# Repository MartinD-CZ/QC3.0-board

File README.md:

# QC3.0 board
*see the article [here](http://embedblog.eu/?p=504). Also available on [Tindie](https://www.tindie.com/products/martind/quick-charge-qc-30-buck-converter-board/).*

Board with a switching buck converter and a QC 3.0 class-A chip (it also supports FastCharge, DCP, and others).

## Features:
* HiSilicon Fast Charging Protocol (FCP), ie Huawei phones (tested)
* Qualcomm Quick Charge 2.0/3.0 Class A: up to 12 V Output Voltage (tested)
* USB DCP (shorting D+ Line to D-) per USB Battery Charging Specification, Revision 1.2 (tested)
* USB DCP (applying 2.7V on D+ Line and 2.7V on D- Line), ie Apple 12 W
* USB DCP (applying 1.2V on D+ and D- Lines)
* Chinese Telecommunication Industrial Standard YD/T 1591-2009 (whatever that is, I have not tested that)

## Specs:
* input voltage: 6 - 15 V, recommended 12 - 15 V
* input current: max 2 A
* output current: max 2 A
* efficiency (Vin = 12 V, Vout = 5 V, Iout = 1 A): 95 %
* efficiency (Vin = 12 V, Vout = 5 V, Iout = 2 A): 92 %
* quiescent current (no load connected, Vin = 12 V): 800 µA

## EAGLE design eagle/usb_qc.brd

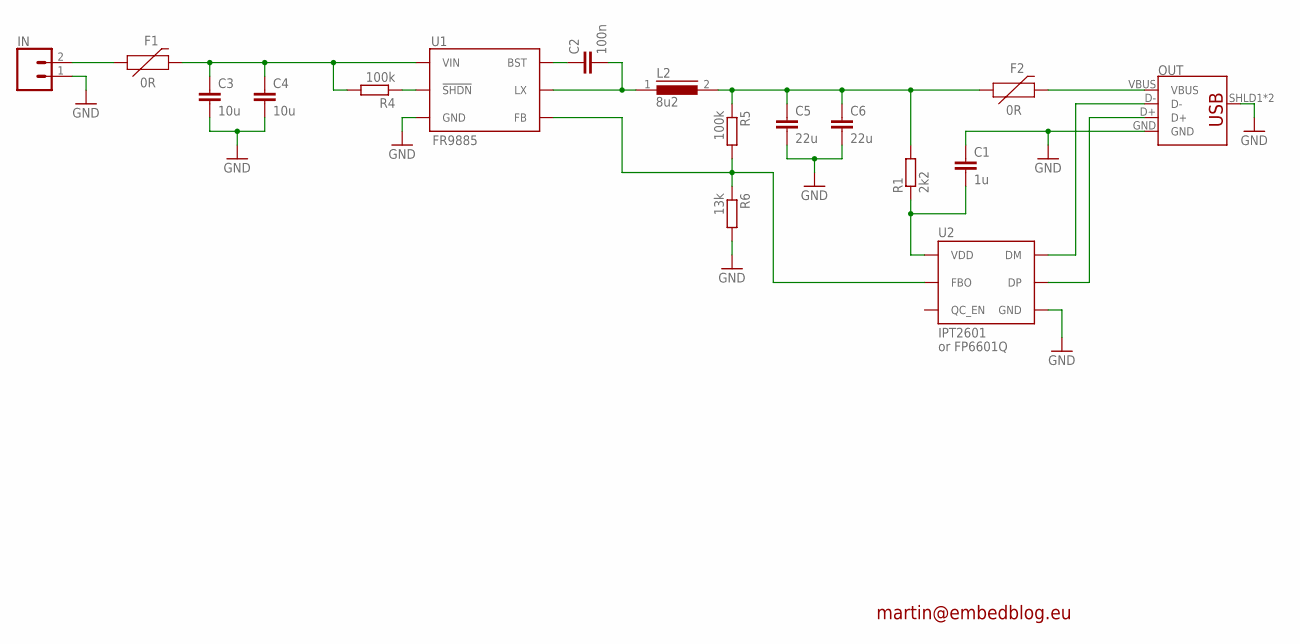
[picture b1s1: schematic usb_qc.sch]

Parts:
C1: 1u; C1206
C2: 100n; C1206
C3, C4: 10u; C1206
C5, C6: 22u; C1206
F1, F2: 0R; 1206
IN: 5MM_SCREWTERMINAL_LARGE; SCREWTERMINAL-5MM-2
L2: 8u2; DR73
OUT: USB_A_REVERSED; USB-A-S-SILK-FEMALE
R1: 2k2; R1206
R4, R5: 100k; R1206
R6: 13k; R1206
U1: FR9885; SOT23-6
U2: IPT2601; SOT23-6

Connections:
FB: R5.2, R6.1, U1.3 (FB), U2.3 (FBO)
GND: C1.1, C3.2, C4.2, C5.2, C6.2, IN.1, OUT.GND, OUT.SHLD1 (SHIELD), OUT.SHLD2 (SHIELD), R6.2, U1.2 (GND), U2.2 (GND)
LX: C2.2, L2.1, U1.6 (LX)
unnamed: OUT.D-, U2.6 (DM)
unnamed: OUT.D+, U2.1 (DP)
unnamed: F1.1, IN.2
unnamed: C3.1, C4.1, F1.2, R4.2, U1.5 (VIN)
unnamed: R4.1, U1.4 (!SHDN)
unnamed: C5.1, C6.1, F2.1, L2.2, R1.2, R5.1
unnamed: C1.2, R1.1, U2.5 (VDD)
unnamed: C2.1, U1.1 (BST)
VBUS: F2.2, OUT.VBUS

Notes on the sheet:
or FP6601Q
martin@embedblog.eu

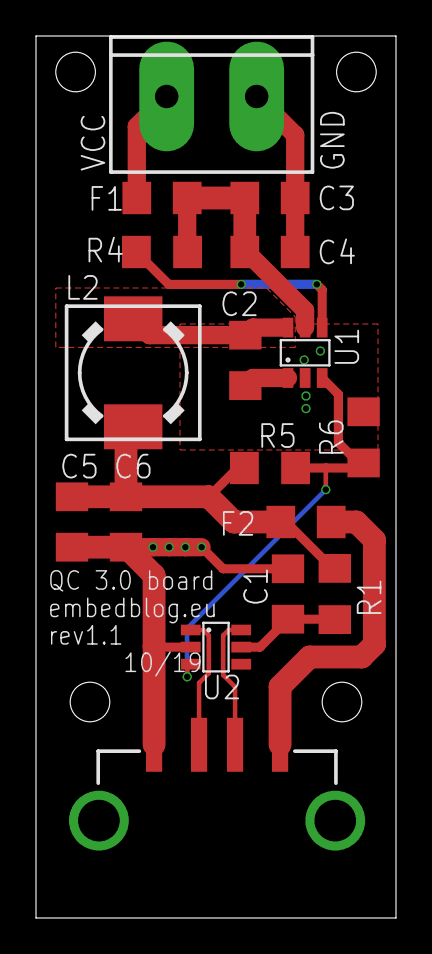
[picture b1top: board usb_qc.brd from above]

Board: 2 copper layers, 20.0 x 49.0 mm, 17 parts (0 on the bottom side), 12 nets.

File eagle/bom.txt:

Part Value                   Device                  Package             Description                                             
C1   1u                      C-EUC1206               C1206               CAPACITOR, European symbol                                                           
C2   100n                    C-EUC1206               C1206               CAPACITOR, European symbol                                                           
C3   10u/16V                 C-EUC1206               C1206               CAPACITOR, European symbol                                                          
C4   10u/16V                 C-EUC1206               C1206               CAPACITOR, European symbol                                                           
C5   22u/16V                 C-EUC1206               C1206               CAPACITOR, European symbol                                                           
C6   22u/16V                 C-EUC1206               C1206               CAPACITOR, European symbol                                                           
F1   0R                      PPTC_HALF-AMP           1206                Resettable Fuse PPTC                                  
F2   0R                      PPTC_HALF-AMP           1206                Resettable Fuse PPTC                                    
IN   5MM_SCREWTERMINAL_LARGE 5MM_SCREWTERMINAL_LARGE SCREWTERMINAL-5MM-2                                                                                      
L2   8u2                     DR73                    DR73                High Power Density, High Efficiency, Shielded Inductors           L                  
OUT  USB_A_REVERSED          USB_A_REVERSED          USB-A-S-SILK-FEMALE                                                                                      
R1   2k2                     R-EU_R1206              R1206               RESISTOR, European symbol                                                            
R4   100k                    R-EU_R1206              R1206               RESISTOR, European symbol                                                            
R5   100k                    R-EU_R1206              R1206               RESISTOR, European symbol                                                            
R6   13k                     R-EU_R1206              R1206               RESISTOR, European symbol                                                            
U1   FR9885                  FR9885                  SOT23-6                                                                                                  
U2   IPT2601                 IPT2601                 SOT23-6

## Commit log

2019-10-25 initial release

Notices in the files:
parts and their libraries:
SparkFun-Fuses: Licensing: Creative Commons ShareAlike 4.0 International - https://creativecommons.org/licenses/by-sa/4.0
